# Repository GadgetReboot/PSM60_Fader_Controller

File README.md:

# PSM60_Fader_Controller
Motorized fader pot controller

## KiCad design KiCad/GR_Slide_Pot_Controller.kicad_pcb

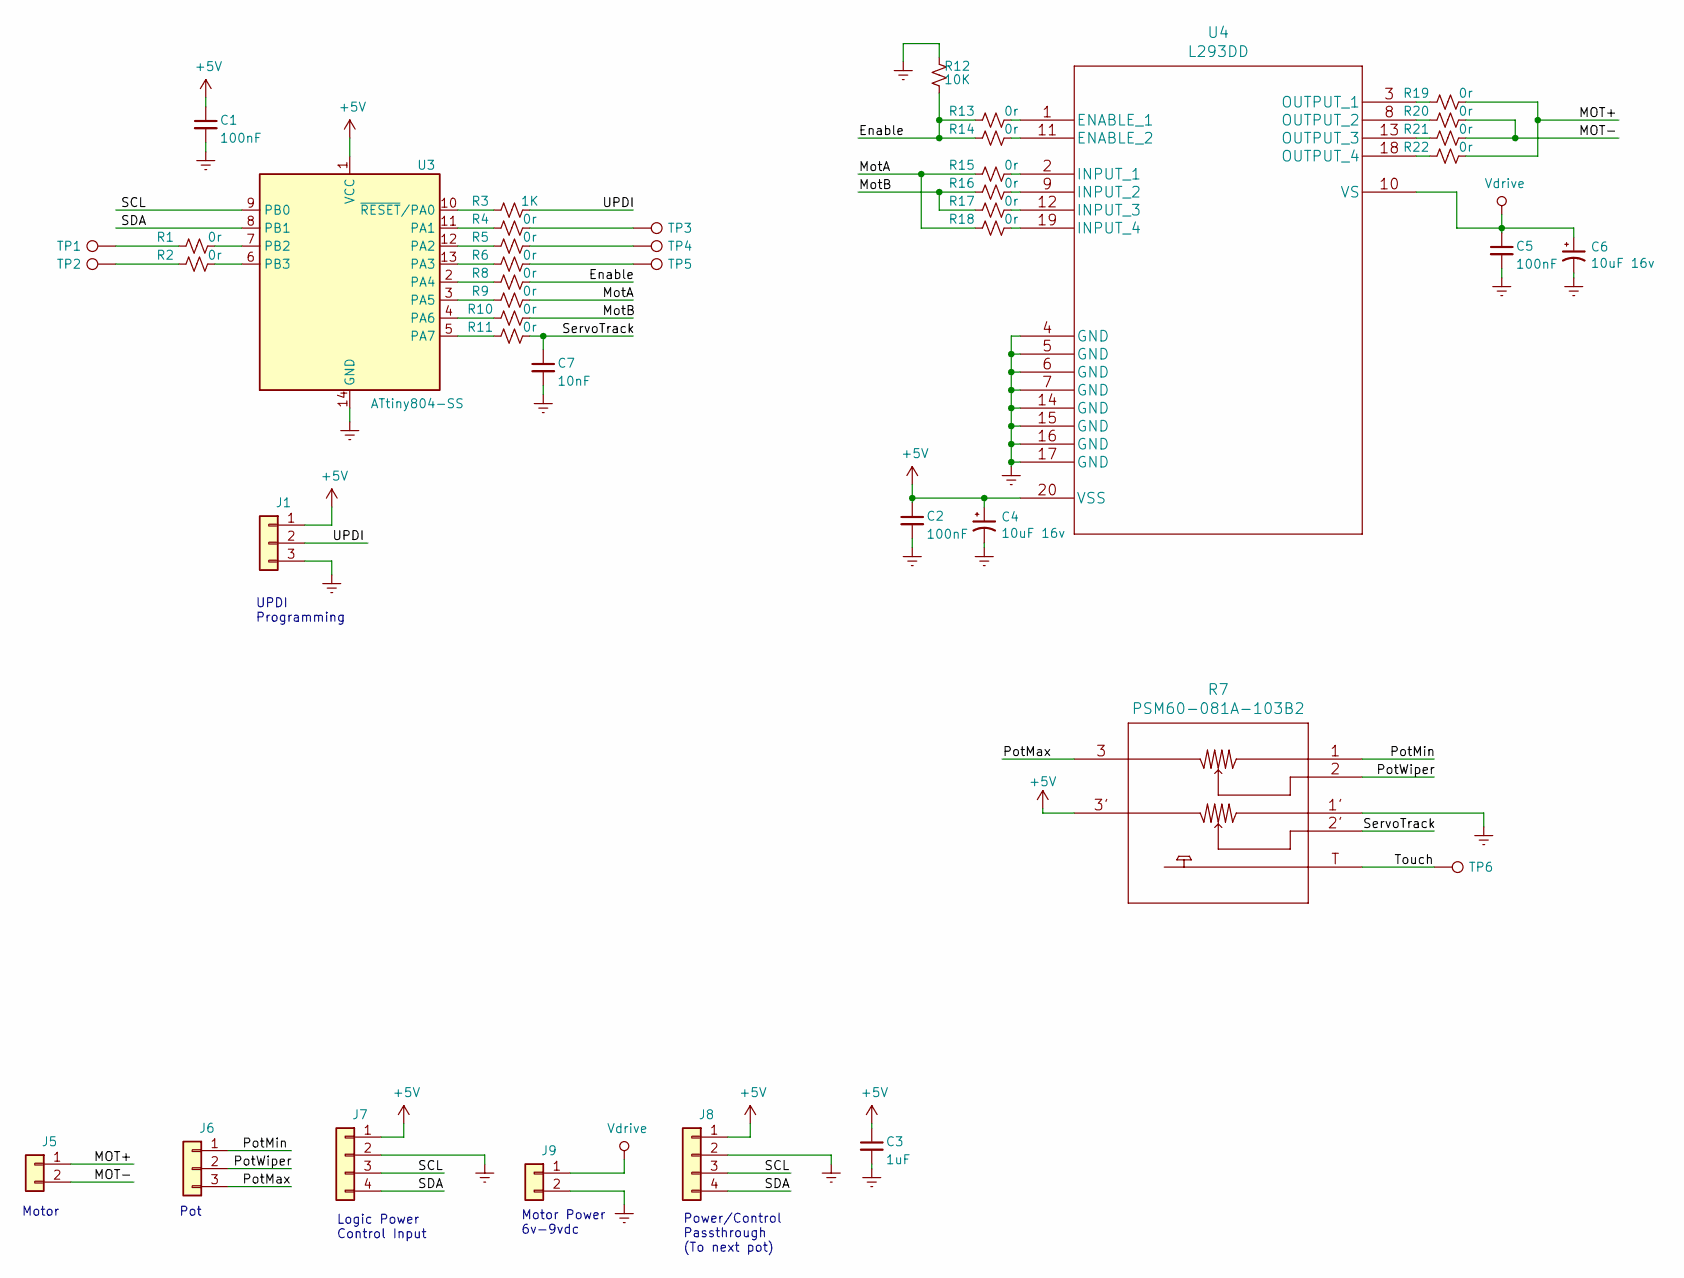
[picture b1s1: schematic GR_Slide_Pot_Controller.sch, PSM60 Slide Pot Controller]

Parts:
C1, C2, C5: 100nF; C_0805_2012Metric_Pad1.15x1.40mm_HandSolder
C3: 1uF; C_0805_2012Metric_Pad1.15x1.40mm_HandSolder
C4, C6: 10uF 16v; C_Elec_4x5.4
C7: 10nF; C_0805_2012Metric_Pad1.15x1.40mm_HandSolder
J1: Conn_01x03; PinHeader_1x03_P2.54mm_Vertical
J5, J9: Conn_01x02; JST_XH_S2B-XH-A-1_1x02_P2.50mm_Horizontal
J6: Conn_01x03; JST_XH_S3B-XH-A-1_1x03_P2.50mm_Horizontal
J7, J8: Conn_01x04; JST_XH_S4B-XH-A-1_1x04_P2.50mm_Horizontal
R1, R2, R4, R5, R6, R8, R9, R10, R11, R13, R14, R15, R16, R17, R18, R19, R20, R21, R22: 0r; R_0603_1608Metric_Pad1.05x0.95mm_HandSolder
R3: 1K; R_0805_2012Metric_Pad1.15x1.40mm_HandSolder
R7: PSM60-081A-103B2
R12: 10K; R_0805_2012Metric_Pad1.15x1.40mm_HandSolder
TP1, TP2, TP3, TP4, TP5, TP6: TestPoint; TestPoint_Pad_D1.0mm
U3: ATtiny804-SS; SOIC-14_3.9x8.7mm_P1.27mm
U4: L293DD

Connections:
+5V: C1.1, C2.1, C3.1, C4.1, J1.1, J7.1, J8.1, R7.3' (3_2), U3.1 (VCC), U4.20 (VSS)
/Enable: R8.1, R12.1, R13.2, R14.2
/MOT+: J5.1, R19.1, R22.1
/MOT-: J5.2, R20.1, R21.1
/MotA: R9.1, R15.2, R18.2
/MotB: R10.1, R16.2, R17.2
/PotMax: J6.3, R7.3
/PotMin: J6.1, R7.1
/PotWiper: J6.2, R7.2
/SCL: J7.3, J8.3, U3.9 (PB0)
/SDA: J7.4, J8.4, U3.8 (PB1)
/ServoTrack: C7.1, R7.2' (2_2), R11.1
/Touch: R7.T, TP6.1
/UPDI: J1.2, R3.1
GNDREF: C1.2, C2.2, C3.2, C4.2, C5.2, C6.2, C7.2, J1.3, J7.2, J8.2, J9.2, R7.1' (1_2), R12.2, U3.14 (GND), U4.4 (GND), U4.5 (GND), U4.6 (GND), U4.7 (GND), U4.14 (GND), U4.15 (GND), U4.16 (GND), U4.17 (GND)
unnamed: R1.1, U3.7 (PB2)
unnamed: R1.2, TP1.1
unnamed: R2.1, U3.6 (PB3)
unnamed: R2.2, TP2.1
unnamed: R3.2, U3.10 (~RESET~/PA0)
unnamed: R4.1, TP3.1
unnamed: R4.2, U3.11 (PA1)
unnamed: R5.1, TP4.1
unnamed: R5.2, U3.12 (PA2)
unnamed: R6.1, TP5.1
unnamed: R6.2, U3.13 (PA3)
unnamed: R8.2, U3.2 (PA4)
unnamed: R9.2, U3.3 (PA5)
unnamed: R10.2, U3.4 (PA6)
unnamed: R11.2, U3.5 (PA7)
unnamed: R13.1, U4.1 (ENABLE_1)
unnamed: R14.1, U4.11 (ENABLE_2)
unnamed: R15.1, U4.2 (INPUT_1)
unnamed: R16.1, U4.9 (INPUT_2)
unnamed: R17.1, U4.12 (INPUT_3)
unnamed: R18.1, U4.19 (INPUT_4)
unnamed: R19.2, U4.3 (OUTPUT_1)
unnamed: R20.2, U4.8 (OUTPUT_2)
unnamed: R21.2, U4.13 (OUTPUT_3)
unnamed: R22.2, U4.18 (OUTPUT_4)
Vdrive: C5.1, C6.1, J9.1, U4.10 (VS)

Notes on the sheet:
Motor
Pot
Logic Power Control Input
Power/Control Passthrough (To next pot)
Motor Power 6v-9vdc
UPDI Programming

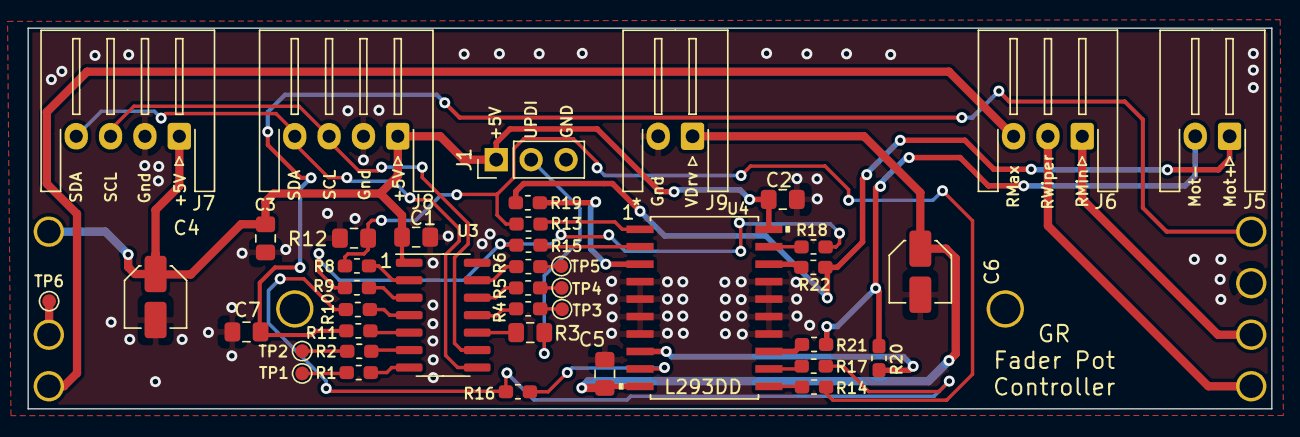
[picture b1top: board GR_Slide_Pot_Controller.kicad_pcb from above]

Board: 2 copper layers, 90.5 x 27.7 mm, 43 parts (1 on the bottom side), 41 nets.

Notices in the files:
parts and their libraries:
Copyright 2021 Accelerated Designs. All rights reserved.
